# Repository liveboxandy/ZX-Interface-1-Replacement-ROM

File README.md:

# ZX-Interface-1-Replacement-ROM
Replacement ROM for the ZX Interface 1

The original ROM for the ZX Interface 1 is a mask programmed device that is now obsolete. This work is based on an idea by Retroleum and others in using a flash device on a PCB in order to remap the pins to suit the original 24 pin device layout. When using the suggested Samtec pins there is just enough room in the Interface 1 to allow the use of Samtec sockets so the ROM can be removed if required. I have not found any other pins that are short enough to allow the use of a socket in the Interface 1. 

This PCB will support SST39SF010, SST39SF020 and SST39SF040 devices and will allow up to a maximum of 32 different ROM images to be used.

The orignal ROM is an 8K device but if address A13 is taken from the ROM and connected to A13 on the expansion BUS then the 16K ROM image by Ian Collier can be used. See picture for location of address A13 on the edge connector of the ZX Interface 1.

This has been updated to Kicad 9 and requires an adaptor board to remap the pins when programming.

The adapter board is available under ZX-Interface-1-Replacement-ROM-Programming-Adapter.

Comments - Good Bad or indifferent on https://www.facebook.com/groups/zxspa/

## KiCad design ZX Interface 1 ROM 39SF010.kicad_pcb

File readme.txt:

Address Lines Avalable

Addr Hex  Dec  Max
A18 40000 256K 512K SST39SF040 Pulled Hi in Operation
A17 20000 128K 256K SST39SF020 Pulled Hi in Operation
A16 10000  64K 128K SST39SF010 Switched Hi/Lo by switch on my board.Pulled Lo by short to Ground on Retroleum.
A15  8000  32K  64K Switched Hi/Lo by switch on Retroleum.
A14  4000  16K  32K Pulled Hi in Operation
A13  2000   8K  16K Pulled Hi in Operation. Allows 16K Operation with wire add.
A12  1000   4K   8K
A11   800   2K   4K
A10   400   1K   2K 
A9    200  512   1K
A8    100  256  512
A7     80  128  256
6      40   64  128
5      20   32   64
4      10   16   32
3       8    8   16
2       4    4    8
1       2    2    4
0       1    1    2

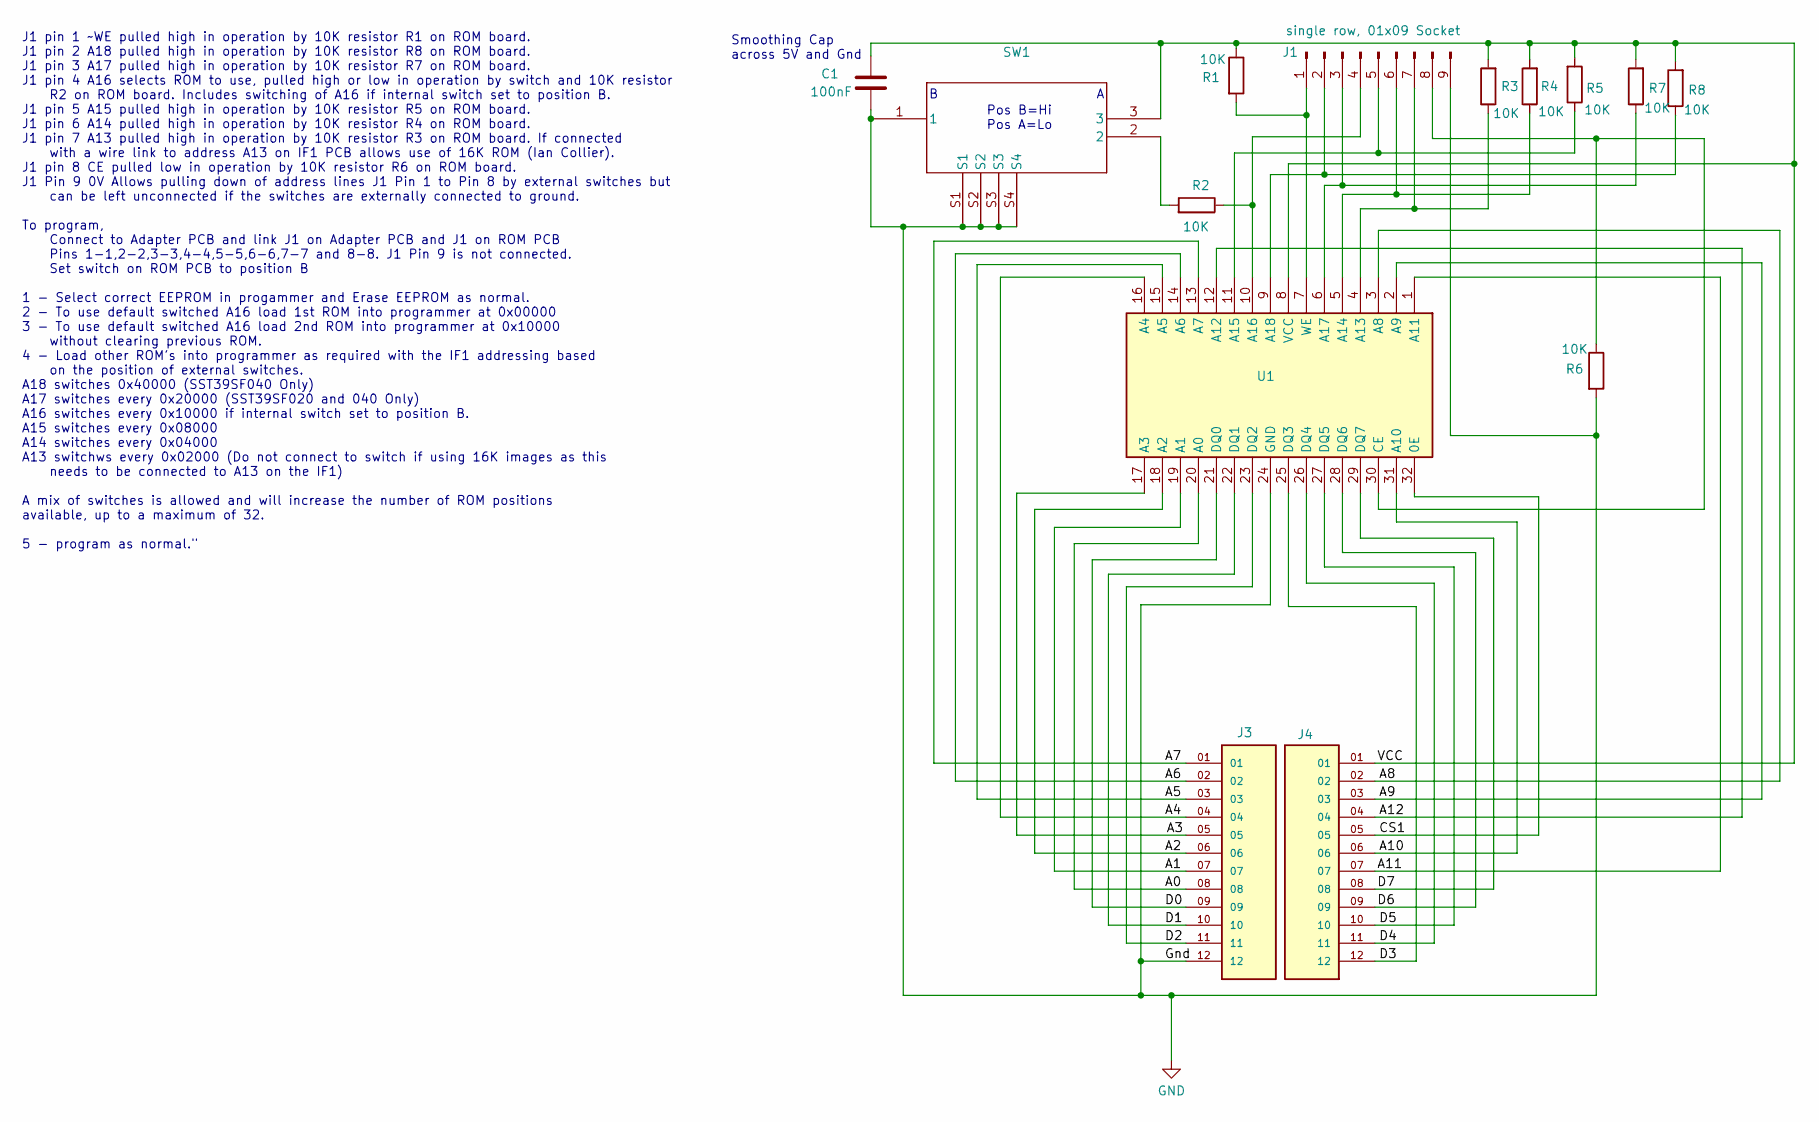
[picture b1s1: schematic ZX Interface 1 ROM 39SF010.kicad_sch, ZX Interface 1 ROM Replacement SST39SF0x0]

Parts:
C1: 100nF; C_1206_3216Metric_Pad1.33x1.80mm_HandSolder
J1: Conn_01x09_Pin; PinSocket_1x09_P2.54mm_HorizontalR
J3, J4: BBL-112-G-E; Pin-Pin Header 2.54mm Round Samtec BBL-112-G-E; PARTREV R
R1, R2, R3, R4, R5, R6, R7, R8: 10K; R_1206_3216Metric_Pad1.30x1.75mm_HandSolder
SW1: SW_SPDT; SW_PCM12SMTR
U1: SST39SF040A TSOP; TSOP-I-32_12.4x8mm_P0.5mm

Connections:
/A0: J3.08, U1.20 (A0)
/A1: J3.07, U1.19 (A1)
/A2: J3.06, U1.18 (A2)
/A3: J3.05, U1.17 (A3)
/A4: J3.04, U1.16 (A4)
/A5: J3.03, U1.15 (A5)
/A6: J3.02, U1.14 (A6)
/A7: J3.01, U1.13 (A7)
/A8: J4.02, U1.3 (A8)
/A9: J4.03, U1.2 (A9)
/A10: J4.06, U1.31 (A10)
/A11: J4.07, U1.1 (A11)
/A12: J4.04, U1.12 (A12)
/CS1: J4.05, U1.32 (0E)
/D0: J3.09, U1.21 (DQ0)
/D1: J3.10, U1.22 (DQ1)
/D2: J3.11, U1.23 (DQ2)
/D3: J4.12, U1.25 (DQ3)
/D4: J4.11, U1.26 (DQ4)
/D5: J4.10, U1.27 (DQ5)
/D6: J4.09, U1.28 (DQ6)
/D7: J4.08, U1.29 (DQ7)
/VCC: C1.1, J4.01, R1.1, R3.2, R4.2, R5.2, R7.2, R8.2, SW1.3, U1.8 (VCC)
GND: C1.2, J1.9, J3.12, R6.2, SW1.1, SW1.S1, SW1.S2, SW1.S3, SW1.S4, U1.24 (GND)
unnamed: J1.1, R1.2, U1.7 (WE)
unnamed: J1.2, R8.1, U1.9 (A18)
unnamed: J1.3, R7.1, U1.6 (A17)
unnamed: J1.4, R2.1, U1.10 (A16)
unnamed: J1.5, R5.1, U1.11 (A15)
unnamed: J1.6, R4.1, U1.5 (A14)
unnamed: J1.7, R3.1, U1.4 (A13)
unnamed: J1.8, R6.1, U1.30 (CE)
unnamed: R2.2, SW1.2

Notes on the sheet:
J1 pin 1 ~WE pulled high in operation by 10K resistor R1 on ROM board. J1 pin 2 A18 pulled high in operation by 10K resistor R8 on ROM board. J1 pin 3 A17 pulled high in operation by 10K resistor R7 on ROM board. J1 pin 4 A16 selects ROM to use, pulled high or low in operation by switch and 10K res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
Pos B=Hi Pos A=Lo
Smoothing Cap across 5V and Gnd

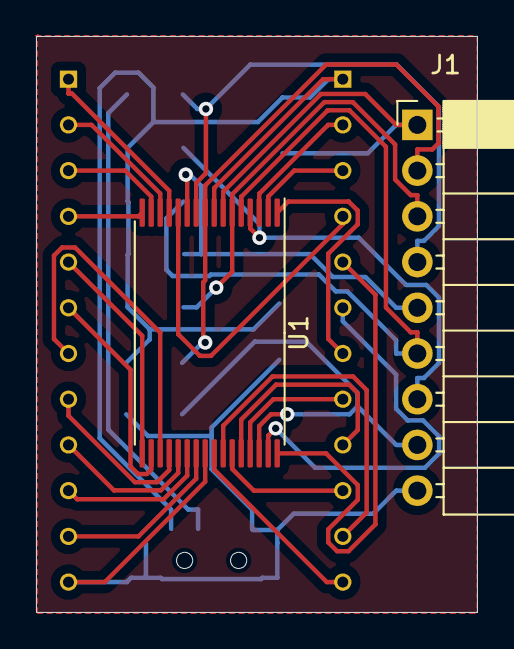
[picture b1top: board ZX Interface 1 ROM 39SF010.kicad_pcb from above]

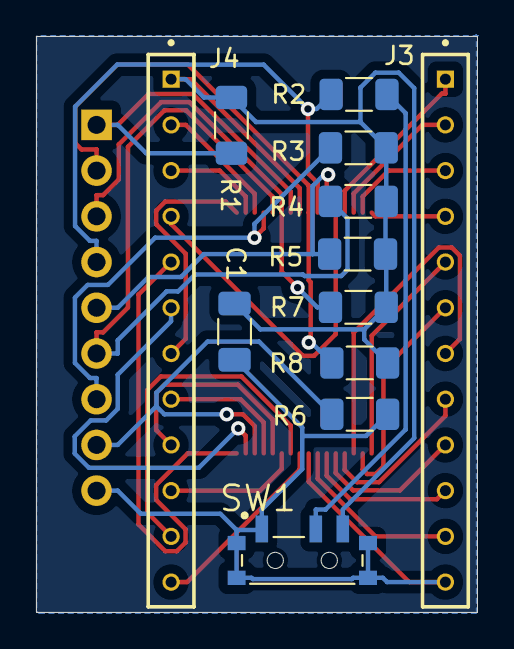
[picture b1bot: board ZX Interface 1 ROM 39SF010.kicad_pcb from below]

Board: 2 copper layers, 24.5 x 32.0 mm, 14 parts (12 on the bottom side), 33 nets.

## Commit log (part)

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2023-11-28 Initial README.md
2023-11-28 Update ZX Interface 1 ROM 39SF010.kicad_sch
    Correct max number of ROM's to 32 not 64.
2023-11-30 Updated to use Right Angle 9 pin Header
2025-10-22 Add files via upload
    Updated file to Kicad 9. Restructured folders. Added ibom (Interactive BOM)
2025-10-26 Fix ROM Addresses for Programming
    Correct default addresses for programming and add table for address decoding
2025-10-26 Update PCB picture
